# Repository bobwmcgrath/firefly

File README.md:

# firefly
This code has two loops, sense and shine.  In shine, the IR LED blinks on and off really really fast.  In sense the led is off and the sensor (an IR photo transistor) is read at the rate of LED blinking.  Then there is a debouncing algorythem.. or a more apropriatly rebouncing algorythem that makes sure each sensor value alternates being higher or lower than the previouse sensor value.  When this is the case some number of times in a row, another led blinking has been detected.  When blnking is detected the counter that defines the lengeth of the loop is multiplied by 1.1 casuing the sense loop to end sooner untill the LEDs are in sync.  Currently the design works on an arduino at a range of 2' to 4' in a dimly lit room.  

Things to do:

optimize for low power consumption

figure out how well this will work with more than 2 fireflys

more percise timing may be accomplished with interupts

add an asyncronus loop that makes a green LED fade in and out in phase with the other loops

add a function to sleep during the day

design final board

spec final components

add a phase locking mechansism to compensate for clock drift.  

Usefull links:

programing the attiny10

http://www.technoblogy.com/show?1YQY

http://junkplusarduino.blogspot.com/p/attiny10-resources.html

Attiny10 Datasheet

http://ww1.microchip.com/downloads/en/DeviceDoc/atmel-8127-avr-8-bit-microcontroller-attiny4-attiny5-attiny9-attiny10_datasheet.pdf

grant proposal

https://docs.google.com/document/d/1ZPEneeNdc6gHhQVbn35usS5zam0JfSeI3uuNZ7ygSEo/edit?usp=sharing

Photo transistor schematic

https://www.digikey.com/-/media/Images/Article%20Library/TechZone%20Articles/2018/September/How%20to%20Use%20Photodiodes%20and%20Phototransistors%20Most%20Effectively/article-2018september-how-to-use-fig3.jpg?ts=77b9d89e-30c2-4136-898a-1c47026af6cd&la=en-US

project insperation

https://www.youtube.com/watch?v=ix66tQ93bdU

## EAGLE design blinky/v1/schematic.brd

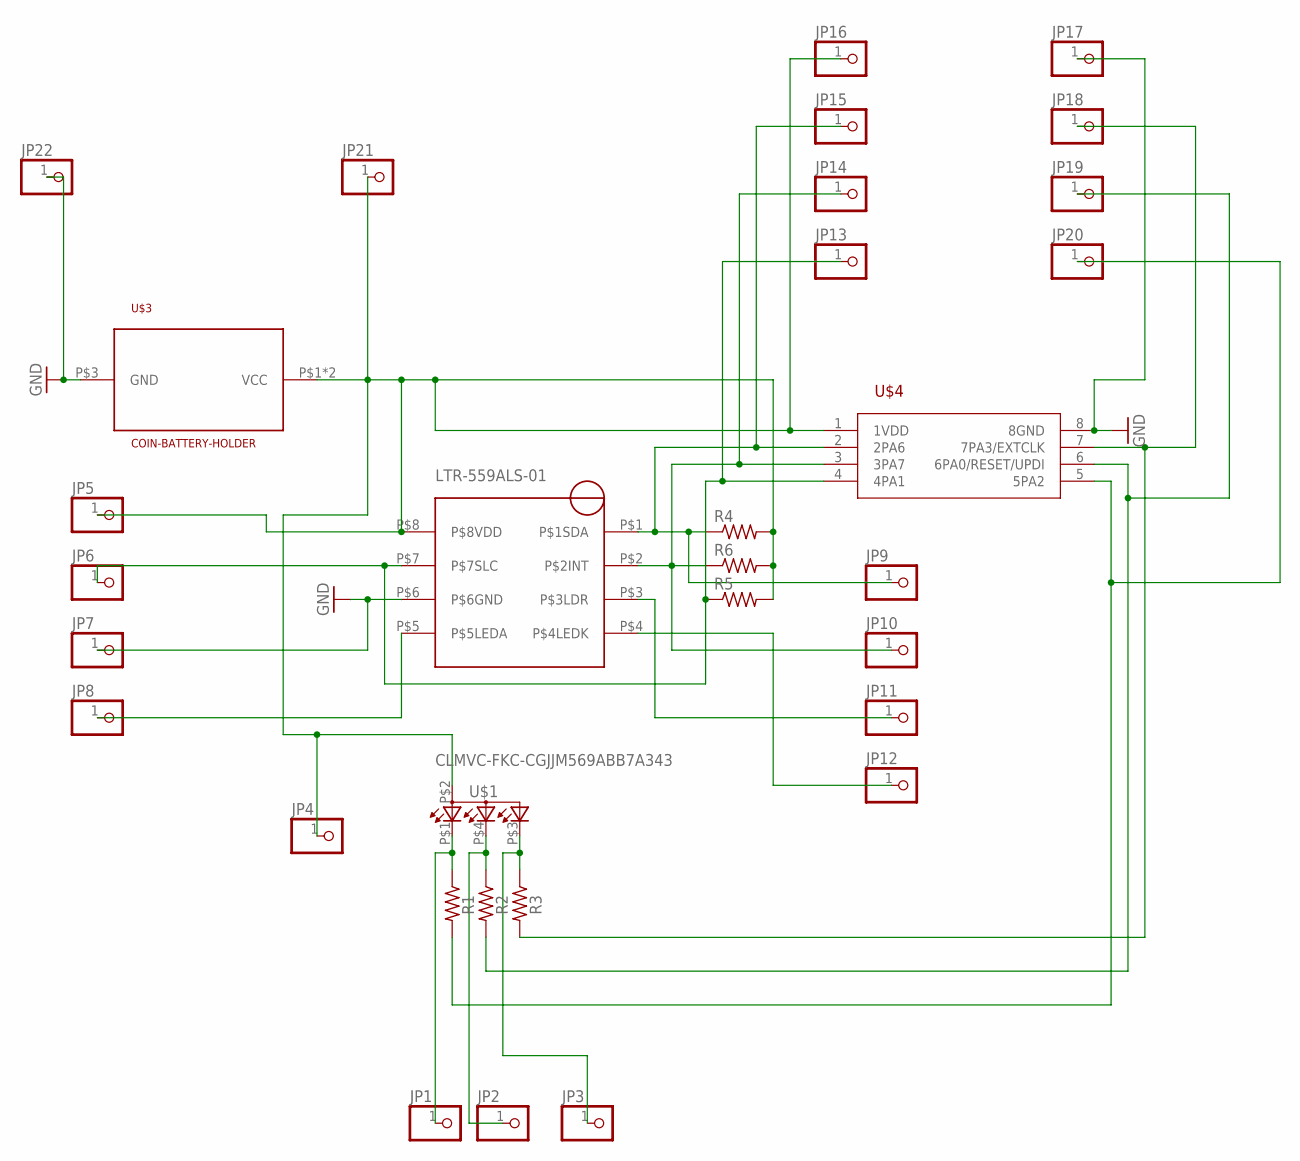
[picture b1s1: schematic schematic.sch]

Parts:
JP1, JP2, JP3, JP4, JP5, JP6, JP7, JP8, JP9, JP10, JP11, JP12, JP13, JP14, JP15, JP16, JP17, JP18, JP19, JP20, JP21, JP22: PINHD-1X1; 1X01
R1, R2, R3, R4, R5, R6: R-US_R0805; R0805
U$1: CLMVC-FKC-CGJJM569ABB7A343
U$2: LTR-559ALS-01
U$3: COIN-BATTERY-HOLDER; 3034_C
U$4: ATTINY402-SSNR; SOIC127P600X175-8N

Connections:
GND: JP7.1, JP17.1, JP22.1, U$2.P$6 (P$6GND), U$3.P$3 (GND), U$4.8 (8GND)
unnamed: JP3.1, R3.1, U$1.P$3 (CGREEN)
unnamed: JP2.1, R2.1, U$1.P$4 (CBLUE)
unnamed: JP1.1, R1.1, U$1.P$1 (CRED)
unnamed: JP8.1, U$2.P$5 (P$5LEDA)
unnamed: JP18.1, R3.2, U$4.7 (7PA3/EXTCLK)
unnamed: JP19.1, R2.2, U$4.6 (6PA0/RESET/UPDI)
unnamed: JP20.1, R1.2, U$4.5 (5PA2)
unnamed: JP9.1, JP15.1, R4.1, U$2.P$1 (P$1SDA), U$4.2 (2PA6)
unnamed: JP10.1, JP14.1, R6.1, U$2.P$2 (P$2INT), U$4.3 (3PA7)
unnamed: JP6.1, JP13.1, R5.1, U$2.P$7 (P$7SLC), U$4.4 (4PA1)
unnamed: JP4.1, JP5.1, JP16.1, JP21.1, R4.2, R5.2, R6.2, U$1.P$2 (GND), U$2.P$8 (P$8VDD), U$3.P$1 (VCC), U$3.P$2 (VCC), U$4.1 (1VDD)
unnamed: JP11.1, U$2.P$3 (P$3LDR)
unnamed: JP12.1, U$2.P$4 (P$4LEDK)

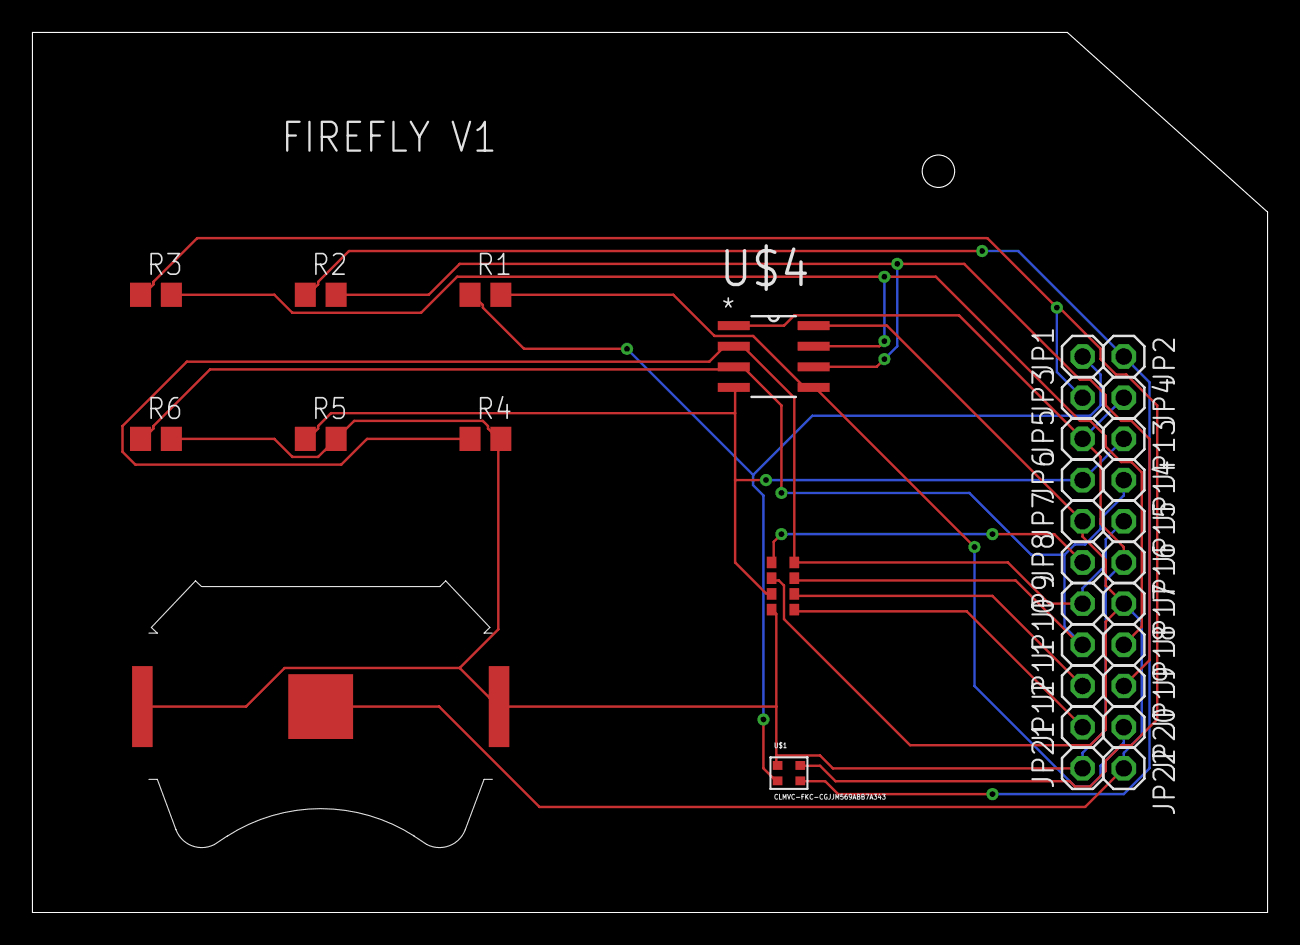
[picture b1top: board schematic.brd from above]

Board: 2 copper layers, 76.2 x 54.3 mm, 32 parts (0 on the bottom side), 14 nets.

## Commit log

2019-02-16 added EAGLE files and readme
2019-04-03 First draft C code for the ATTiny10, examples, and a programmer using arduino
    one variable does not like to be higher than 11
2019-04-03 Old code for the flora sensor on arduino
2019-04-03 Working arduino code with a photo transistor and an IR LED
    Using the serial out put completely breaks the timing.
2019-04-03 updated to do, added links
2019-04-05 while loops
2019-05-03 Some clean up, more comments.
    Added hypothetical code for daylight detection.
2019-05-03 fixed reference error in daytime detection
2019-05-03 Added a whole lot of code to try to correct for clock drift. By commenting out line 186 (fix_delay in the main loop), we avoid actually using the code, and the memory it takes up, but can see if ever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
2019-05-17 Does anybody read Chinese?
    For various reasons I would like to source this sub 2 cent battery holder, but I don't know and Chinese.
2019-05-19 faster loop, daytime detection
    reverted from previous
2019-05-19 added dayFlag and fade
    the ir LED fades wether in bright light of not, and the green LED does nothing weather in bright light or not
2019-05-19 fixed shine() - you were returning a global variable
2019-05-19 no dayFlag
    I did it without day flag. works good enough.
2019-05-19 no reason to have the shineCounter+=1 in both if{} and else{}?
2019-05-21 Cleaned up and commented, no changes to code.
2019-05-25 changed to 4ms cycle
    the sensor is only so fast
2019-06-04 Create digikeyPrintout
2019-06-04 Create digikeyDump
2019-06-04 Create myDump
2019-06-04 Create blankDump
